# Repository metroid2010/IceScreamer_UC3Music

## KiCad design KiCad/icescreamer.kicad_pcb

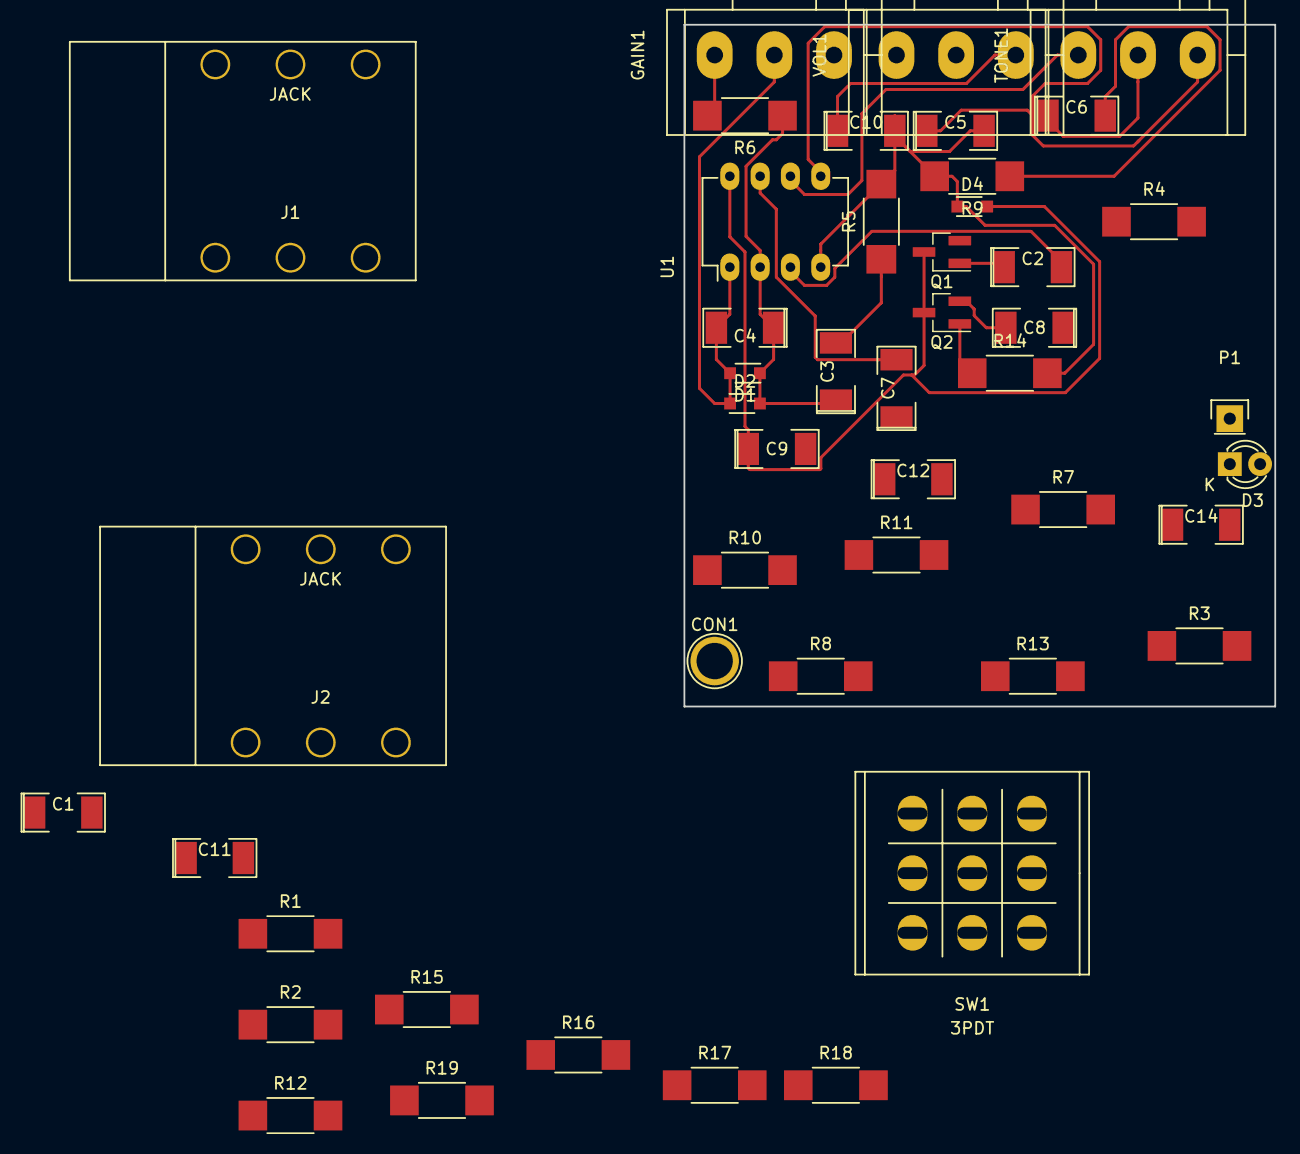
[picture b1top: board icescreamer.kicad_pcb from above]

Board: 2 copper layers, 49.5 x 57.1 mm, 47 parts (0 on the bottom side), 29 nets.

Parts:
C1: 0.02uF; SMD-2010_Pol
C2, C7, C14: 1uF; SMD-2010_Pol
C3: 0.047uF; SMD-2010_Pol
C4: 51pF; SMD-2010_Pol
C5, C6: 0.22uF; SMD-2010_Pol
C8: 0.1Uf; SMD-2010_Pol
C9, C10: 0.1uF; SMD-2010_Pol
C11, C12: 220uF; SMD-2010_Pol
CON1: PWR_IN; 1pin
D1, D2, D4: DIODE; SOD-323_HandSoldering
D3: LED; LED-3MM
GAIN1: 500K; Potentiometer_Alps-RK16-single_largePads
J1, J2: JACK; CONN_Jack_Female_6.35mm_THD
P1: BAT_T; Pin_Header_Straight_1x01
Q1, Q2: NPN; SOT-23_Handsoldering
R1, R7, R10, R11: 1K; R_2010_HandSoldering
R2, R13: 510K; R_2010_HandSoldering
R3, R4, R8, R14, R16, R17, R18: 10K; R_2010_HandSoldering
R5: 4.7K; R_2010_HandSoldering
R6: 51K; R_2010_HandSoldering
R9: 220R; R_2010_HandSoldering
R12: 20K; R_2010_HandSoldering
R15: 100R; R_2010_HandSoldering
R19: 4K7; R_2010_HandSoldering
SW1: 3PDT; Switches_Stomp_Switch_3PDT
TONE1: 20K; Potentiometer_Alps-RK16-single_largePads
U1: TL072; DIP-8_W7.62mm_LongPads
VOL1: 100K; Potentiometer_Alps-RK16-single_largePads

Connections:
+5V: C9.1, C11.1, D3.2, D4.2, Q1.3, Q2.3, R17.1, U1.8
-5V: C5.2, C10.2, C12.2, D4.1, J1.S, J1.TS, J2.S, R3.2, R5.2, R9.2, R14.2, R16.2, R18.2, SW1.6, U1.4
FX in: C1.2, SW1.2
FX out: C14.2, R16.1, SW1.4
GND: C9.2, C10.1, C11.2, C12.1, R2.2, R4.2, R8.1, R12.2, R13.2, R17.2, R18.1, VOL1.3
unnamed: C1.1, R1.1
unnamed: C2.1, Q1.1, R3.1
unnamed: C2.2, R4.1, U1.3
unnamed: C3.1, C4.1, D1.1, D2.2, R6.1, U1.2
unnamed: C3.2, R5.1
unnamed: C4.2, D1.2, D2.1, GAIN1.2, R7.1, U1.1
unnamed: C5.1, R7.2, R8.2, TONE1.3, U1.5
unnamed: C6.1, TONE1.2
unnamed: C6.2, R9.1
unnamed: C7.1, R11.2
unnamed: C7.2, R10.2, U1.7
unnamed: C8.1, R12.1, VOL1.2
unnamed: C8.2, Q2.2, R13.1
unnamed: C14.1, R15.2
unnamed: CON1.1, J1.R
unnamed: D3.1, R19.1
unnamed: GAIN1.1, R6.2
unnamed: J1.T, SW1.5
unnamed: J2.T, SW1.1, SW1.8
unnamed: Q1.2, R1.2, R2.1
unnamed: Q2.1, R14.1, R15.1
unnamed: R10.1, TONE1.1, U1.6
unnamed: R11.1, VOL1.1
unnamed: R19.2, SW1.3

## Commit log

2016-12-25 :boom::camel: Added .gitattributes
2016-12-25 Pseudo-fork from UC3Music repo
    Tried to successfully fork the repo, and failed
2016-12-26 Updated WIP pcb
